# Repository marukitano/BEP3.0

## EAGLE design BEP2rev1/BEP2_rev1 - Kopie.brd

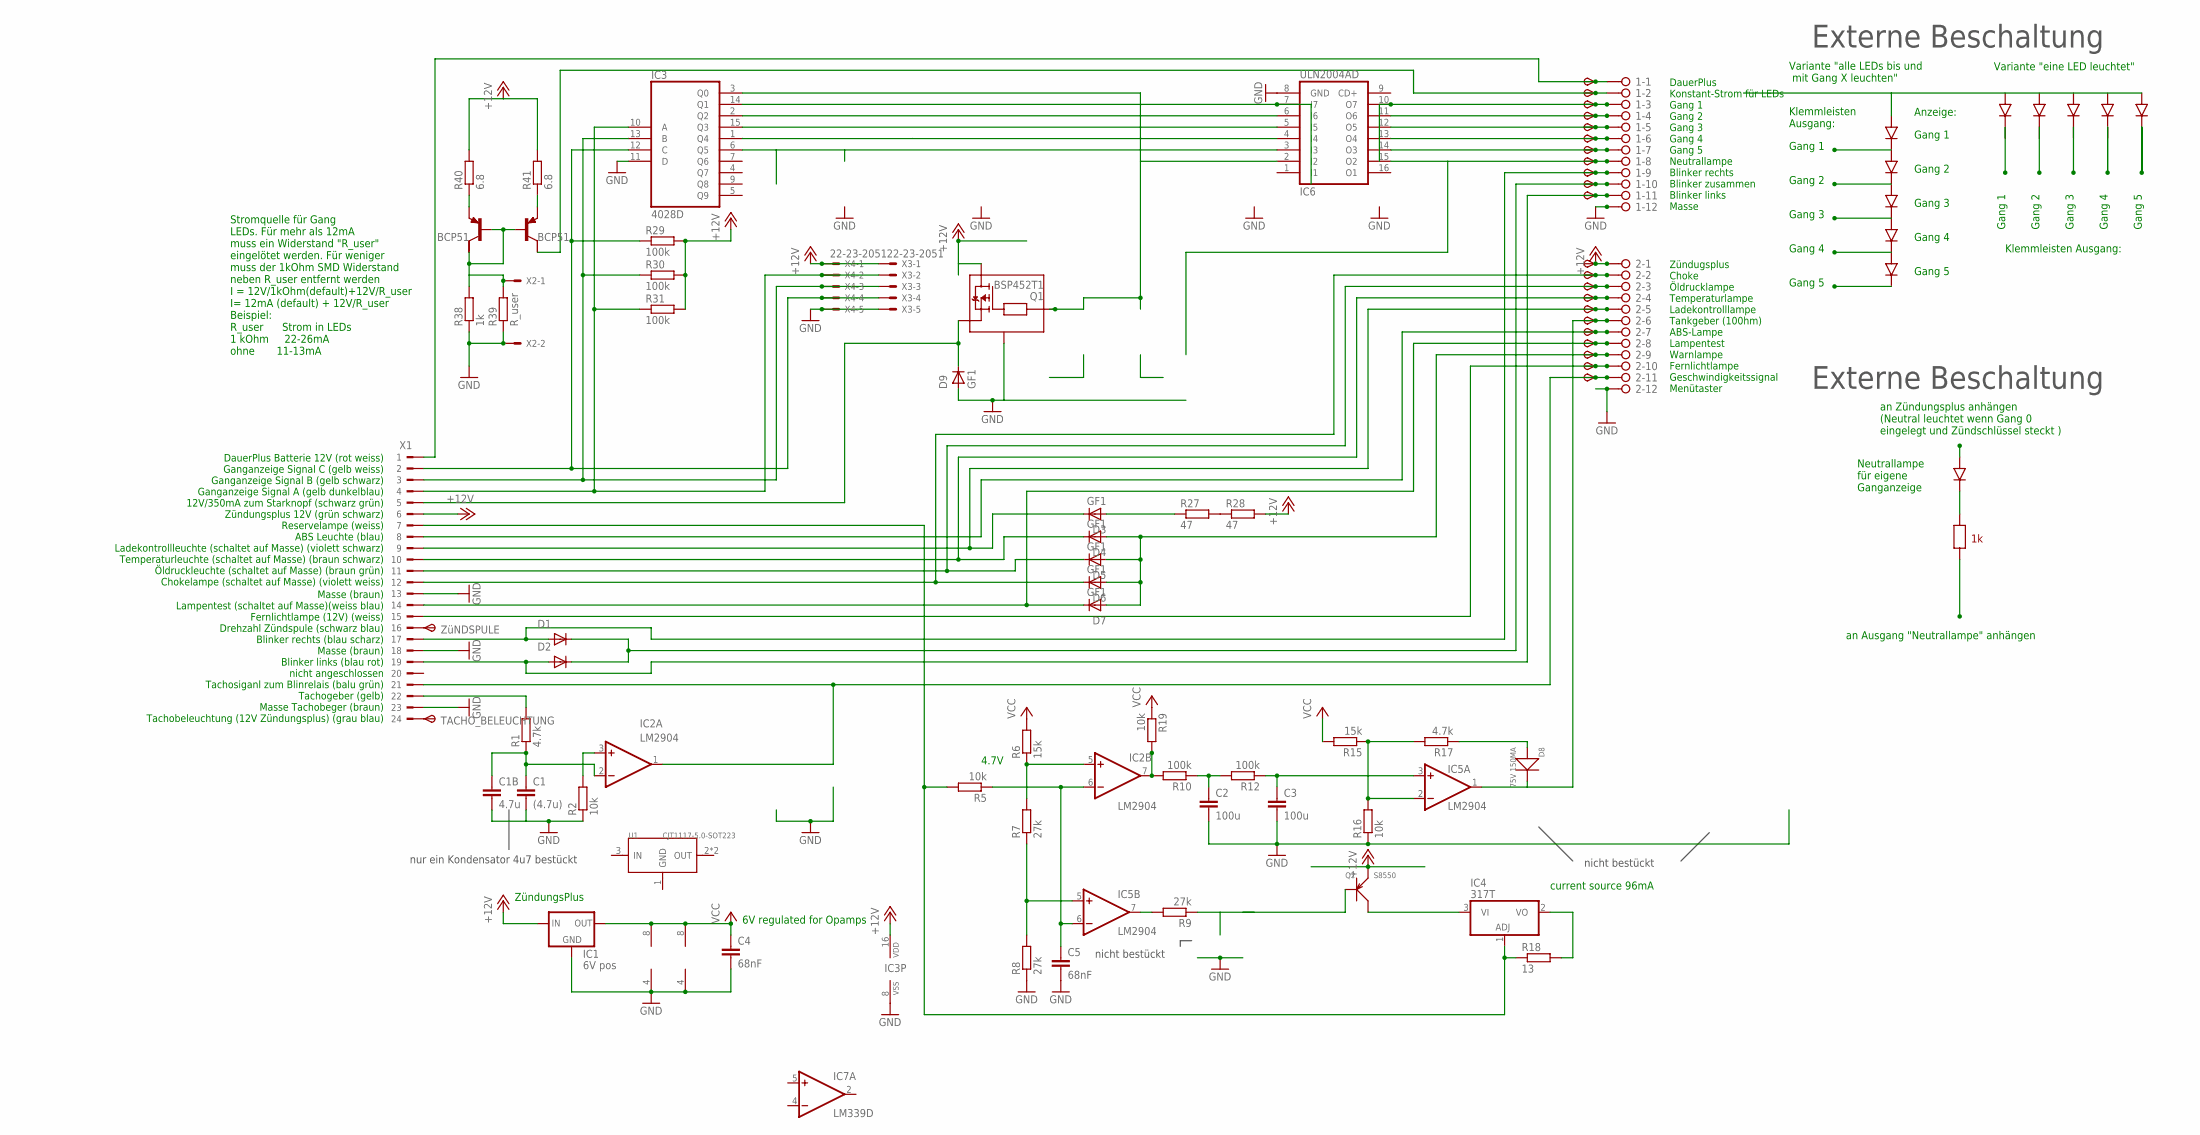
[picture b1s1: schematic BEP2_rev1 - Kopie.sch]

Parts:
1, 2: 2081-1132; 12-PIN
C1: (4.7u); C1206
C1B: 4.7u; C0805K
C2, C3: 100u; C1206K
C4, C5: 68nF; C1206K
D1, D2, D3, D4, D5, D6, D7, D9: GF1; SMA-DO214AC
D8: 75V 150MA; LED-1206
IC1: 6V pos; 78LXX
IC2, IC5: LM2904; SO08
IC3: 4028D; SO16
IC4: 317T; TO220H
IC6: ULN2004AD; SO16
IC7: LM339D; SO14
Q1: BSP452T1; SOT223
Q2: S8550; SOT-23
R1, R17: 4.7k; R0805
R2, R5, R16, R19: 10k; R0805
R6, R15: 15k; R0805
R7, R8, R9: 27k; R0805
R10, R12, R29, R30, R31: 100k; R0805
R18: 13; 0207/10
R27, R28: 47; V235/17
R38: 1k; R0805
R39: R_user; R0805
R40, R41: 6.8; R0805
T13, T14: BCP53T1; SOT223
TACHO_BELEUCHTUNG: TPSP1_1MM; P1_1.0MM
TP1, TP2, TP3, TP4, TP5, TP6, TP7, TP8, TP9, TP10, TP11, TP12, TP16, TP17, TP18, TP19, TP21, TP22, TP23, TP24, TP25, TP26: TPSB1,27; B1,27
U1: CJT1117-5.0-SOT223; SOT-223
X1: CON_BMW; 24-PIN
X2: 22-23-2021
X3, X4: 22-23-2051
ZüNDSPULE: TPSP1_1MM; P1_1.0MM

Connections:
+12V: 2.1, IC1.IN, IC3.16 (VDD), Q1.4 (V+), Q2.2 (E), R28.2, R29.2, R30.2, R31.2, R40.2, R41.2, TP12.TP, X1.6, X3.1, X4.1
GND: 1.12, 2.12, C1.2, C1B.2, C2.2, C3.2, C4.2, C5.2, D9.A, IC1.GND, IC2.4 (V-), IC3.8 (VSS), IC3.11 (D), IC5.4 (V-), IC6.8 (GND), IC7.12 (GND), Q1.2 (GND), R2.1, R8.1, R16.1, R38.1, R39.1, X1.13, X1.18, X1.23, X2.2, X3.5, X4.5
unnamed: 2.9, D4.A, D5.A, D6.A, D7.A, TP24.TP
unnamed: IC3.10 (A), R31.1, X1.4, X3.2, X4.2
unnamed: IC3.13 (B), R30.1, X1.3, X3.3, X4.3
unnamed: 2.7, TP22.TP, X1.8
unnamed: IC3.3 (Q0), IC6.2 (I2), Q1.3 (IN)
unnamed: IC2.3 (+IN), R2.2
unnamed: R27.2, R28.1
unnamed: D9.K (C), Q1.1 (OUT), X1.5
unnamed: 2.2, D6.K (C), TP16.TP, X1.12
unnamed: 2.3, D5.K (C), TP17.TP, X1.11
unnamed: 2.4, D4.K (C), TP18.TP, X1.10
unnamed: IC4.1 (ADJ), R5.2, R18.1, X1.7
unnamed: C5.1, IC2.6 (-IN), IC5.6 (-IN), R5.1
unnamed: IC3.12 (C), R29.1, X1.2, X3.4, X4.4
unnamed: IC3.15 (Q3), IC6.5 (I5)
unnamed: 2.8, D7.K (C), TP23.TP, X1.14
unnamed: 1.9, D1.A, TP9.TP, X1.17
unnamed: 1.11, D2.A, TP11.TP, X1.19
unnamed: 1.10, D1.K (C), D2.K (C), TP10.TP
unnamed: R1.2, X1.22
unnamed: C1.1, C1B.1, IC2.2 (-IN), R1.1
unnamed: 1.6, IC6.13 (O4), TP6.TP
unnamed: 1.7, IC6.14 (O3), TP7.TP
unnamed: 2.11, IC2.1 (OUT), TP26.TP, X1.21
unnamed: IC4.2 (VO), R18.2
unnamed: IC5.5 (+IN), R7.1, R8.2
unnamed: IC5.7 (OUT), R9.2
unnamed: IC4.3 (VI), Q2.3 (C)
unnamed: Q2.1 (B), R9.1
unnamed: IC3.14 (Q1), IC6.7 (I7)
unnamed: IC3.2 (Q2), IC6.6 (I6)
unnamed: 1.5, IC6.12 (O5), TP5.TP
unnamed: IC2.5 (+IN), R6.1, R7.2
unnamed: IC2.7 (OUT), R10.2, R19.2
unnamed: X1.16, ZüNDSPULE.TP
unnamed: C2.1, R10.1, R12.2
unnamed: C3.1, IC5.3 (+IN), R12.1
unnamed: IC5.2 (-IN), R15.1, R16.2, R17.2
unnamed: D8.+, R17.1
unnamed: 1.8, IC6.15 (O2), TP8.TP
unnamed: 2.10, TP25.TP, X1.15
unnamed: D3.A, R27.1
unnamed: 2.5, D3.K (C), TP19.TP, X1.9
unnamed: TACHO_BELEUCHTUNG.TP, X1.24
unnamed: 1.2, T14.2 (C), TP2.TP
unnamed: 2.6, D8.-, IC5.1 (OUT), TP21.TP
unnamed: IC3.6 (Q5), IC6.3 (I3)
unnamed: 1.4, IC6.11 (O6), TP4.TP
unnamed: 1.3, IC6.10 (O7), TP3.TP
unnamed: R38.2, R39.2, T13.1 (B), T13.2 (C), T14.1 (B), X2.1
unnamed: 1.1, TP1.TP, X1.1
unnamed: R40.1, T13.3 (E)
unnamed: R41.1, T14.3 (E)
V+: IC7.3 (V+)
VCC: C4.1, IC1.OUT, IC2.8 (V+), IC5.8 (V+), R6.2, R15.2, R19.1

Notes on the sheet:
6V regulated for Opamps
current source 96mA
ZündungsPlus
Zündugsplus Choke Öldrucklampe Temperaturlampe Ladekontrolllampe Tankgeber (100hm) ABS-Lampe Lampentest Warnlampe Fernlichtlampe Geschwindigkeitssignal Menütaster
DauerPlus Konstant-Strom für LEDs Gang 1 Gang 2 Gang 3 Gang 4 Gang 5 Neutrallampe Blinker rechts Blinker zusammen Blinker links Masse
DauerPlus Batterie 12V (rot weiss) Ganganzeige Signal C (gelb weiss) Ganganzeige Signal B (gelb schwarz) Ganganzeige Signal A (gelb dunkelblau) 12V/350mA zum Starknopf (schwarz grün) Zündungsplus 12V (grün schwarz) Reservelampe (weiss) ABS Leuchte (blau) Ladekontrollleuchte (schaltet auf Masse) (vi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
Masse (braun) Lampentest (schaltet auf Masse)(weiss blau) Fernlichtlampe (12V) (weiss) Drehzahl Zündspule (schwarz blau) Blinker rechts (blau scharz) Masse (braun) Blinker links (blau rot) nicht angeschlossen Tachosiganl zum Blinrelais (balu grün) Tachogeber (gelb) Masse Tachobeger (braun) Tachobel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
4.7V
Stromquelle für Gang LEDs. Für mehr als 12mA muss ein Widerstand "R_user" eingelötet werden. Für weniger muss der 1kOhm SMD Widerstand neben R_user entfernt werden I = 12V/1kOhm(default)+12V/R_user I= 12mA (default) + 12V/R_user Beispiel: R_user Strom in LEDs 1 kOhm 22-26mA ohne 11-13mA
Gang 1
Gang 2
Gang 3
Gang 4
Gang 5
Variante "eine LED leuchtet"
Variante "alle LEDs bis und mit Gang X leuchten"
Klemmleisten Ausgang:
Klemmleisten Ausgang:
an Zündungsplus anhängen (Neutral leuchtet wenn Gang 0 eingelegt und Zündschlüssel steckt )
an Ausgang "Neutrallampe" anhängen
Neutrallampe für eigene Ganganzeige
Externe Beschaltung
Anzeige:
nicht bestückt
nur ein Kondensator 4u7 bestückt

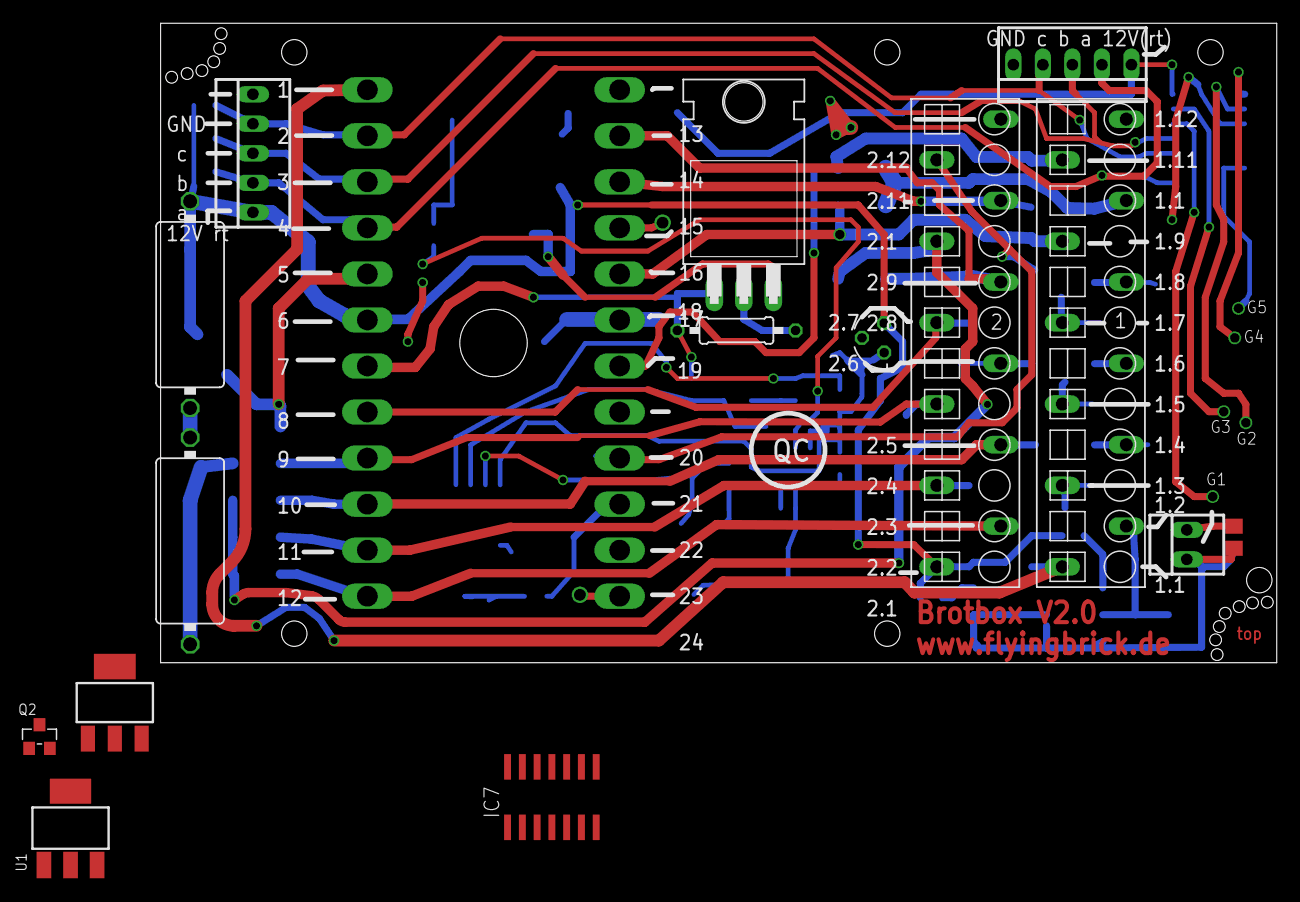
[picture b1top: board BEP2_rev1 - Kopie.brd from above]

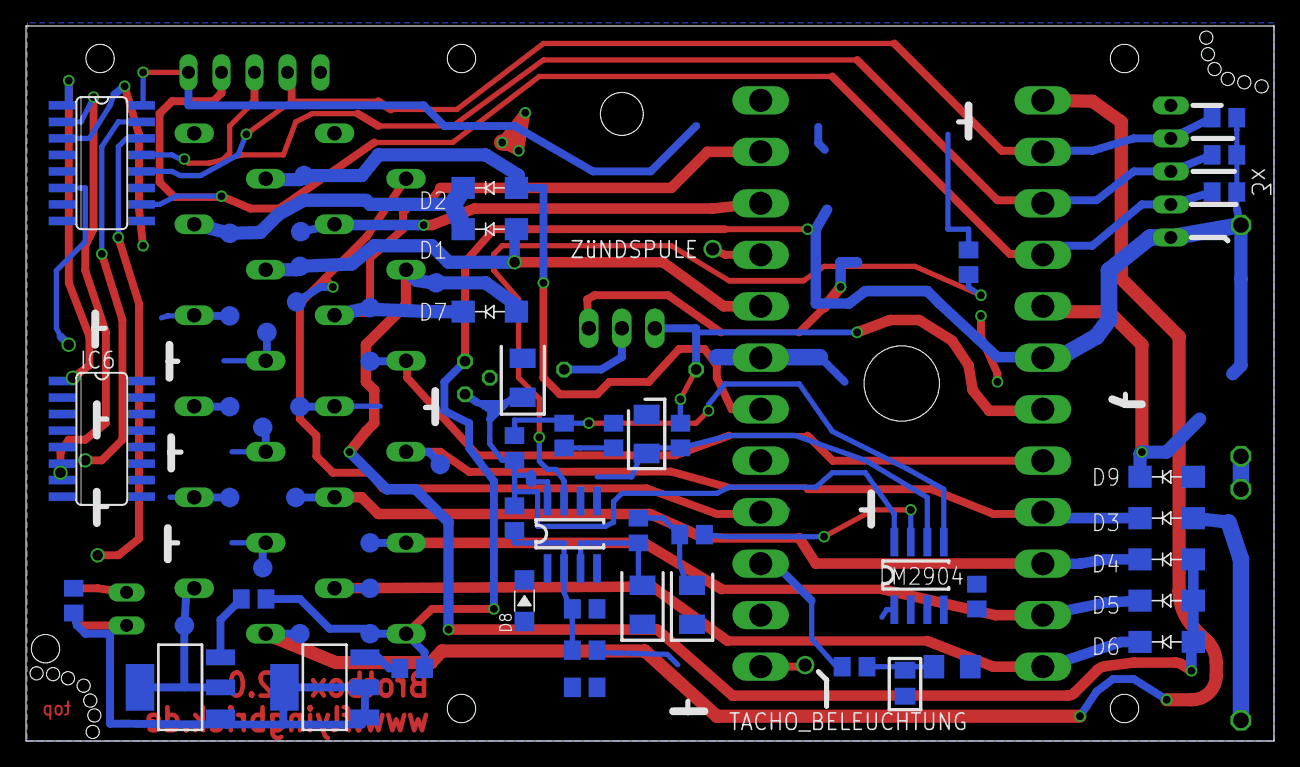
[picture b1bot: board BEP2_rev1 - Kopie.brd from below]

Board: 2 copper layers, 96.0 x 55.0 mm, 80 parts (64 on the bottom side), 56 nets.

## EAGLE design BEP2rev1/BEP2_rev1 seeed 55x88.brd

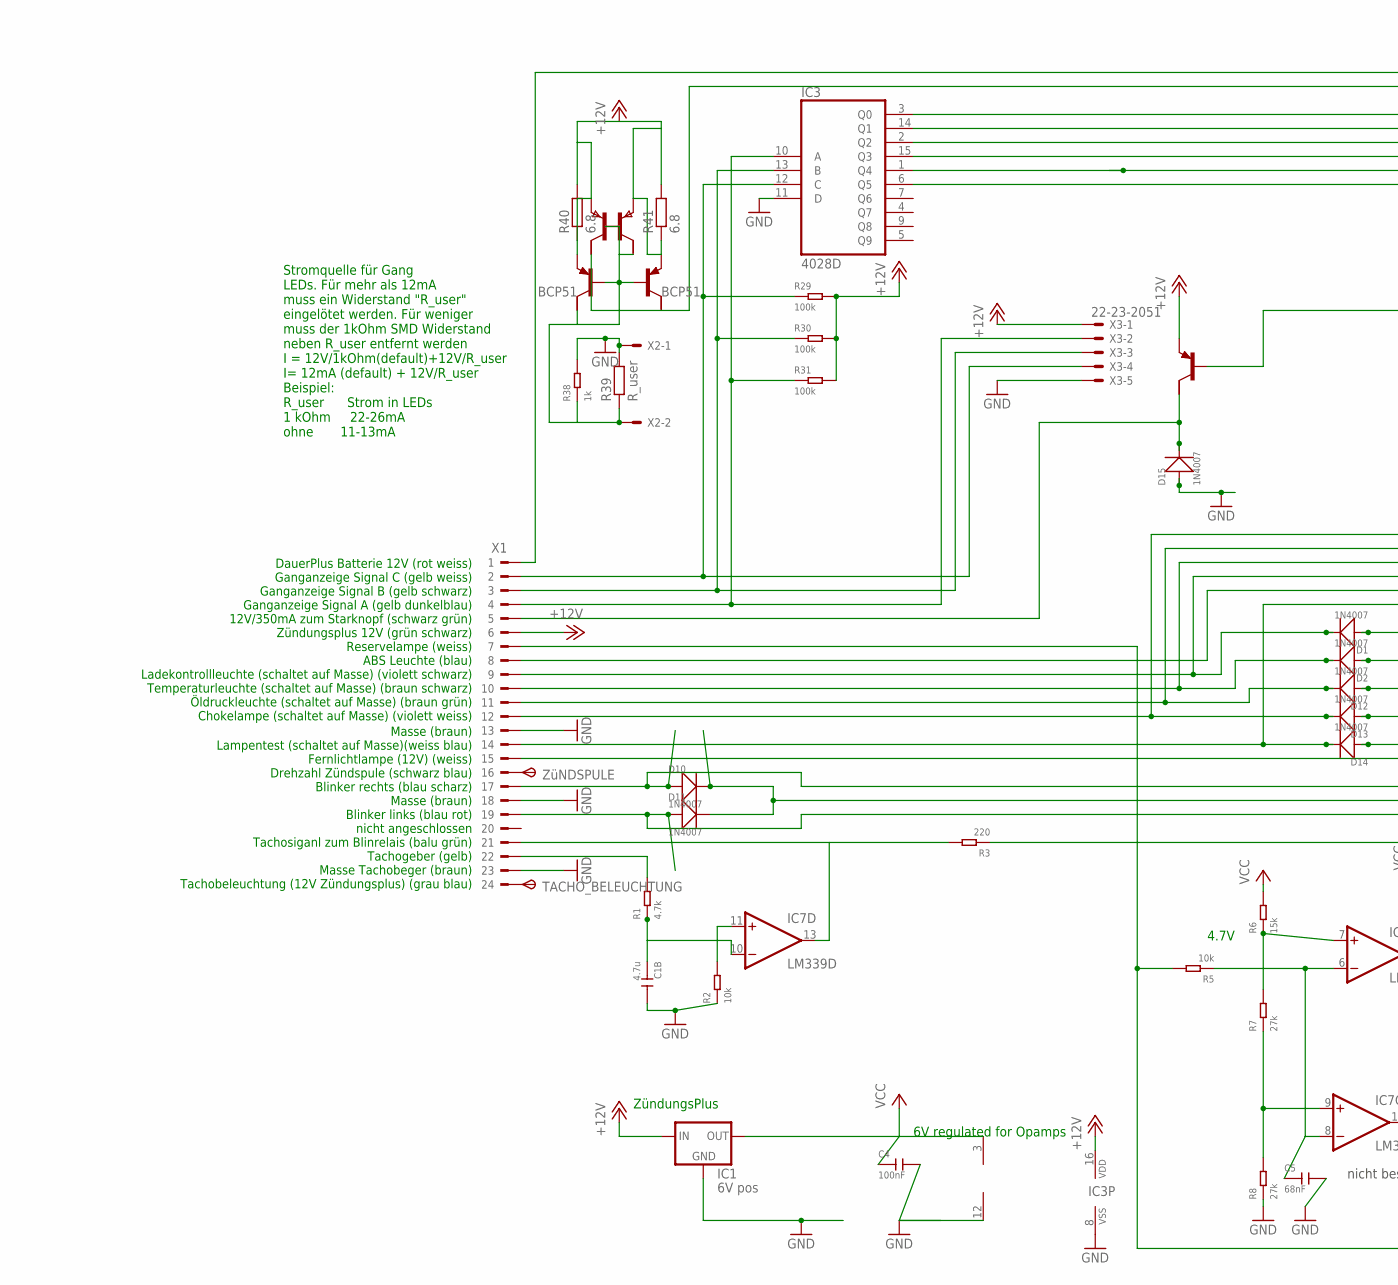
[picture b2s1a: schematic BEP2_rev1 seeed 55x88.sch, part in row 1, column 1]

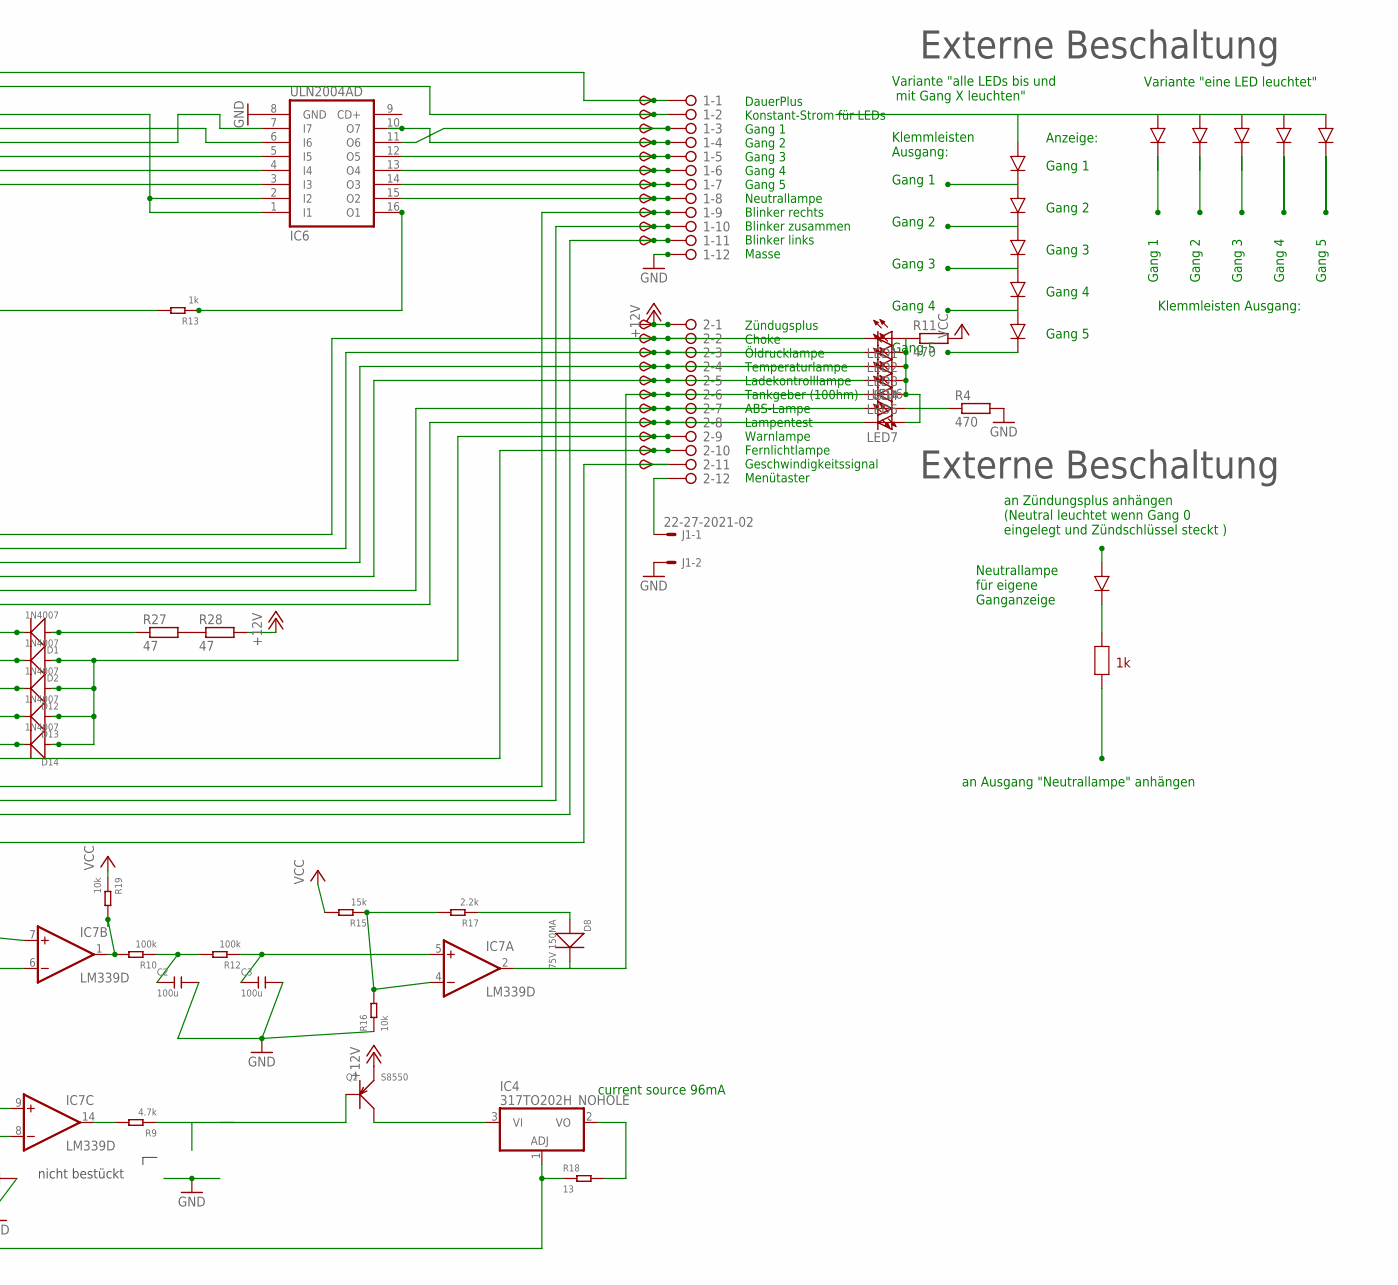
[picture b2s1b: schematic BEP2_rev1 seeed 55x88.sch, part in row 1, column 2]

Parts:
1, 2: 2081-1132; 12-PIN
C1B: 4.7u; C0805
C2, C3: 100u; C1206
C4: 100nF; C0805
C5: 68nF; C0805
D1, D2, D10, D11, D12, D13, D14, D15: 1N4007; DO-214AC
D8: 75V 150MA; LED-1206
IC1: 6V pos; 78LXX
IC3: 4028D; SO16
IC4: 317TO202H_NOHOLE; TO220H_NOHOLE
IC6: ULN2004AD; SO16
IC7: LM339D; SO14
J1: 22-27-2021-02; 6410-02
LED1, LED2, LED3, LED4, LED5, LED6, LED7: LEDLD260; LD260
Q2: S8550; SOT-23
Q3: BCP53T1; SOT223
R1, R9: 4.7k; R0805
R2, R5, R16, R19: 10k; R0805
R3: 220; R0805
R4, R11: 470; R0805
R6: 15k; R0805
R7, R8: 27k; R0603
R10, R12, R29, R30, R31: 100k; R0603
R13, R38: 1k; R0805
R15: 15k; R0603
R17: 2.2k; R0805
R18: 13; R1206
R27, R28: 47; V235/17_1MM
R39: R_user; R0805
R40, R41: 6.8; R0805
T1: PNP2SM8; SM8
T13, T14: BCP53T1; SOT223
TACHO_BELEUCHTUNG: TPSP1_1MM; P1_1.0MM
TP1, TP2, TP3, TP4, TP5, TP6, TP7, TP8, TP9, TP10, TP11, TP12, TP16, TP17, TP18, TP19, TP21, TP22, TP23, TP24, TP25, TP26: TPSB1,27; B1,27
X1: CON_BMW; 24-PIN
X2: 22-23-2021
X3: 22-23-2051
ZüNDSPULE: TPSP1_1MM; P1_1.0MM

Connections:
+12V: 2.1, IC1.IN, IC3.16 (VDD), Q2.2 (E), Q3.3 (E), R28.2, R29.2, R30.2, R31.2, R40.1, R40.2, R41.1, R41.2, T1.1 (E), T1.3 (E), T13.3 (E), T14.3 (E), TP12.TP, X1.6, X3.1
GND: 1.12, C1B.2, C2.2, C3.2, C4.2, C5.2, D15.1 (+), IC1.GND, IC3.8 (VSS), IC3.11 (D), IC6.8 (GND), IC7.12 (GND), J1.2, R2.1, R4.2, R8.1, R16.1, R38.2, R39.2, X1.13, X1.18, X1.23, X2.1, X3.5
unnamed: 2.9, D2.1 (+), D12.1 (+), D13.1 (+), D14.1 (+), TP24.TP
unnamed: IC3.10 (A), R31.1, X1.4, X3.2
unnamed: IC3.13 (B), R30.1, X1.3, X3.3
unnamed: 2.7, LED6.A, TP22.TP, X1.8
unnamed: IC6.16 (O1), R13.1
unnamed: IC7.11 (+IN), R2.2
unnamed: R27.2, R28.1
unnamed: D15.2 (-), Q3.2 (C), X1.5
unnamed: 2.2, D13.2 (-), LED1.K (C), TP16.TP, X1.12
unnamed: 2.3, D12.2 (-), LED2.K (C), TP17.TP, X1.11
unnamed: 2.4, D2.2 (-), LED3.K (C), TP18.TP, X1.10
unnamed: IC4.1 (ADJ), R5.2, R18.1, X1.7
unnamed: C5.1, IC7.6 (-IN), IC7.8 (-IN), R5.1
unnamed: IC3.12 (C), R29.1, X1.2, X3.4
unnamed: IC3.15 (Q3), IC6.5 (I5)
unnamed: 2.8, D14.2 (-), LED7.K (C), TP23.TP, X1.14
unnamed: 1.9, D10.1 (+), TP9.TP, X1.17
unnamed: 1.11, D11.1 (+), TP11.TP, X1.19
unnamed: 1.10, D10.2 (-), D11.2 (-), TP10.TP
unnamed: R1.2, X1.22
unnamed: C1B.1, IC7.10 (-IN), R1.1
unnamed: 1.6, IC6.13 (O4), TP6.TP
unnamed: 1.7, IC6.14 (O3), TP7.TP
unnamed: 2.11, R3.1, TP26.TP
unnamed: 2.12, J1.1
unnamed: IC4.2 (VO), R18.2
unnamed: IC7.9 (+IN), R7.1, R8.2
unnamed: IC7.14 (OUT), R9.2
unnamed: LED6.K (C), R4.1
unnamed: IC4.3 (VI), Q2.3 (C)
unnamed: Q2.1 (B), R9.1
unnamed: IC3.2 (Q2), IC6.7 (I7)
unnamed: 1.3, IC6.11 (O6), TP3.TP
unnamed: 1.5, IC6.12 (O5), TP5.TP
unnamed: IC7.7 (+IN), R6.1, R7.2
unnamed: LED1.A, LED2.A, LED3.A, LED4.A, LED5.A, LED7.A, R11.1
unnamed: X1.16, ZüNDSPULE.TP
unnamed: Q3.1 (B), R13.2
unnamed: IC3.3 (Q0), IC6.1 (I1), IC6.2 (I2)
unnamed: C2.1, R10.1, R12.2
unnamed: C3.1, IC7.5 (+IN), R12.1
unnamed: IC7.4 (-IN), R15.1, R16.2, R17.2
unnamed: IC7.13 (OUT), R3.2, X1.21
unnamed: D8.+, R17.1
unnamed: IC3.1 (Q4), IC6.4 (I4)
unnamed: 1.8, IC6.15 (O2), TP8.TP
unnamed: 2.10, TP25.TP, X1.15
unnamed: D1.1 (+), R27.1
unnamed: 2.5, D1.2 (-), LED4.K (C), TP19.TP, X1.9
unnamed: IC3.14 (Q1), IC6.6 (I6)
unnamed: R38.1, R39.1, T1.2 (B), T1.4 (B), T1.6 (C1), T13.1 (B), T13.2 (C), T14.1 (B), X2.2
unnamed: TACHO_BELEUCHTUNG.TP, X1.24
unnamed: 1.2, T1.8 (C1), T14.2 (C), TP2.TP
unnamed: 2.6, D8.-, IC7.2 (OUT), LED5.K (C), TP21.TP
unnamed: IC3.6 (Q5), IC6.3 (I3)
unnamed: 1.4, IC6.10 (O7), TP4.TP
unnamed: 1.1, TP1.TP, X1.1
unnamed: IC7.1 (OUT), R10.2, R19.2
VCC: C4.1, IC1.OUT, IC7.3 (V+), R6.2, R11.2, R15.2, R19.1

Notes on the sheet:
6V regulated for Opamps
current source 96mA
ZündungsPlus
Zündugsplus Choke Öldrucklampe Temperaturlampe Ladekontrolllampe Tankgeber (100hm) ABS-Lampe Lampentest Warnlampe Fernlichtlampe Geschwindigkeitssignal Menütaster
DauerPlus Konstant-Strom für LEDs Gang 1 Gang 2 Gang 3 Gang 4 Gang 5 Neutrallampe Blinker rechts Blinker zusammen Blinker links Masse
DauerPlus Batterie 12V (rot weiss) Ganganzeige Signal C (gelb weiss) Ganganzeige Signal B (gelb schwarz) Ganganzeige Signal A (gelb dunkelblau) 12V/350mA zum Starknopf (schwarz grün) Zündungsplus 12V (grün schwarz) Reservelampe (weiss) ABS Leuchte (blau) Ladekontrollleuchte (schaltet auf Masse) (vi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
Masse (braun) Lampentest (schaltet auf Masse)(weiss blau) Fernlichtlampe (12V) (weiss) Drehzahl Zündspule (schwarz blau) Blinker rechts (blau scharz) Masse (braun) Blinker links (blau rot) nicht angeschlossen Tachosiganl zum Blinrelais (balu grün) Tachogeber (gelb) Masse Tachobeger (braun) Tachobel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
4.7V
Stromquelle für Gang LEDs. Für mehr als 12mA muss ein Widerstand "R_user" eingelötet werden. Für weniger muss der 1kOhm SMD Widerstand neben R_user entfernt werden I = 12V/1kOhm(default)+12V/R_user I= 12mA (default) + 12V/R_user Beispiel: R_user Strom in LEDs 1 kOhm 22-26mA ohne 11-13mA
Gang 1
Gang 2
Gang 3
Gang 4
Gang 5
Variante "eine LED leuchtet"
Variante "alle LEDs bis und mit Gang X leuchten"
Klemmleisten Ausgang:
Klemmleisten Ausgang:
an Zündungsplus anhängen (Neutral leuchtet wenn Gang 0 eingelegt und Zündschlüssel steckt )
an Ausgang "Neutrallampe" anhängen
Neutrallampe für eigene Ganganzeige
Externe Beschaltung
Anzeige:
nicht bestückt

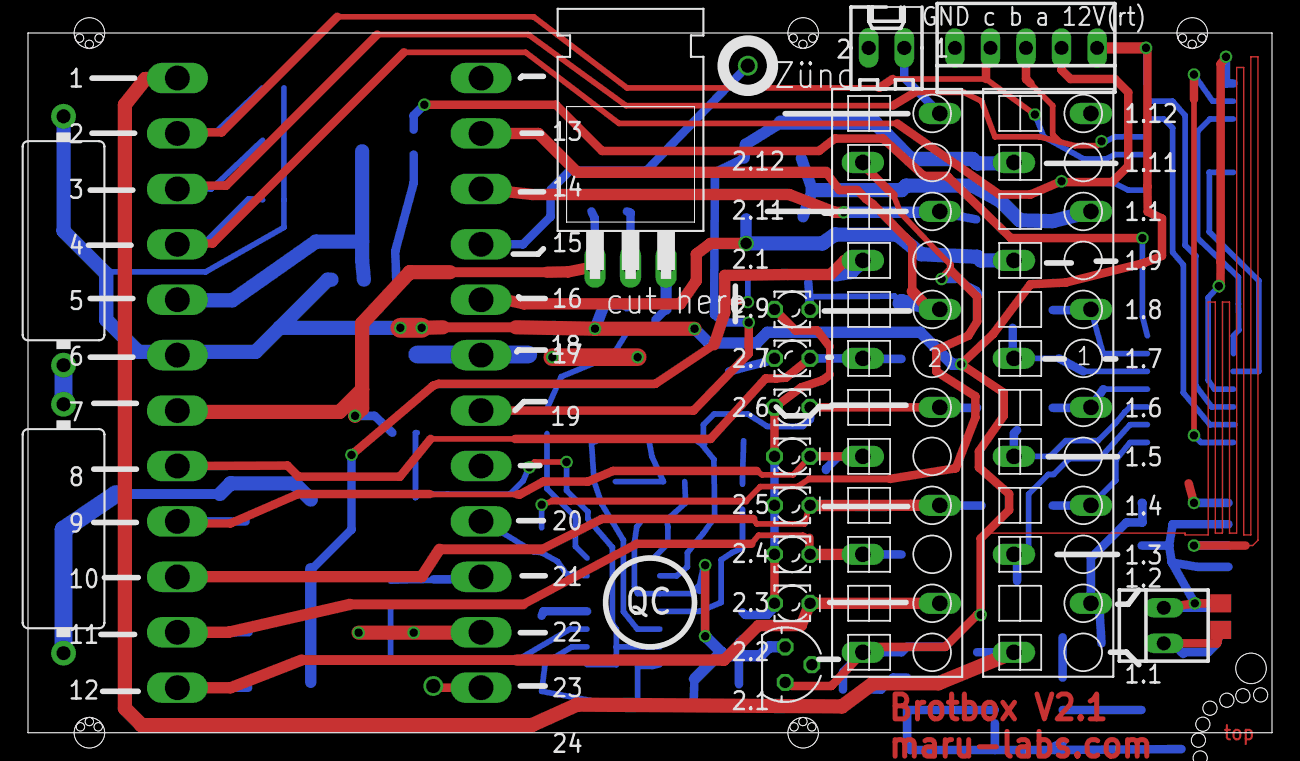
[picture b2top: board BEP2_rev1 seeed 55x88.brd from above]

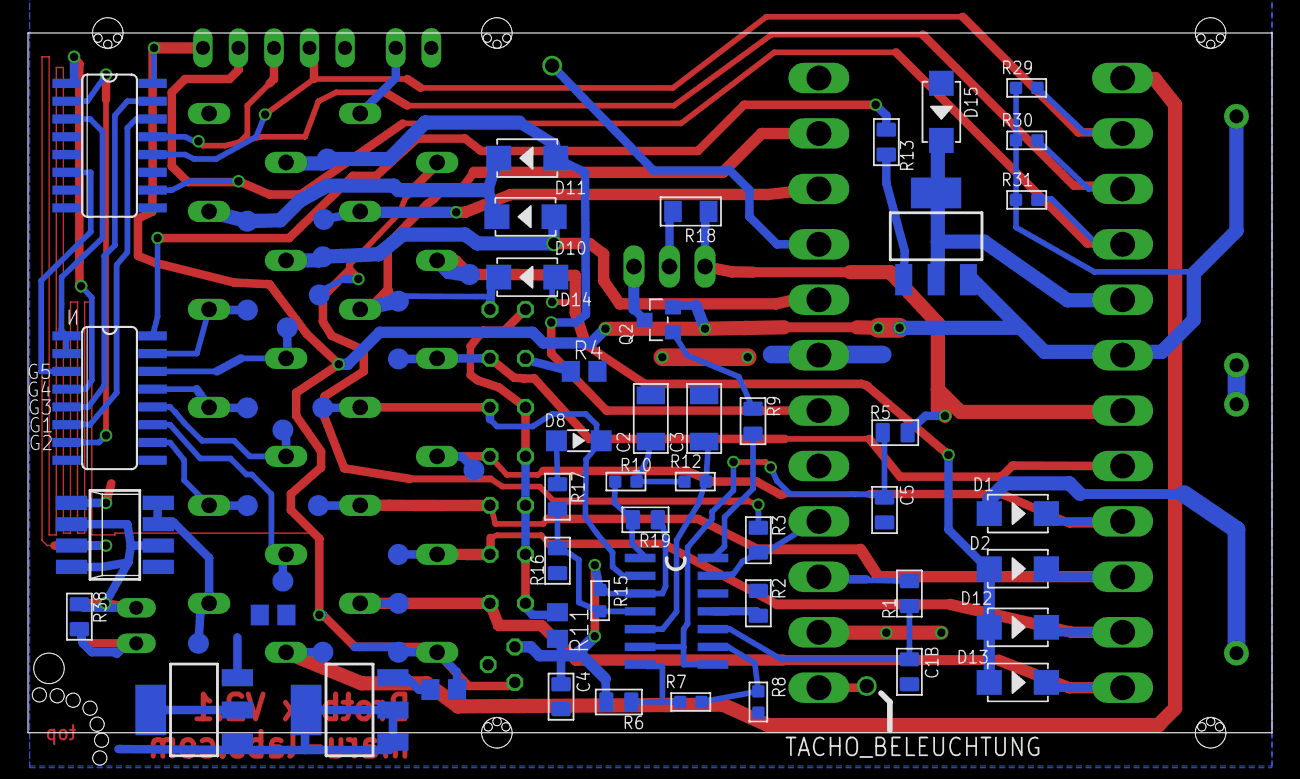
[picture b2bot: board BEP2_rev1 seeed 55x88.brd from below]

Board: 2 copper layers, 88.9 x 50.0 mm, 88 parts (70 on the bottom side), 61 nets.

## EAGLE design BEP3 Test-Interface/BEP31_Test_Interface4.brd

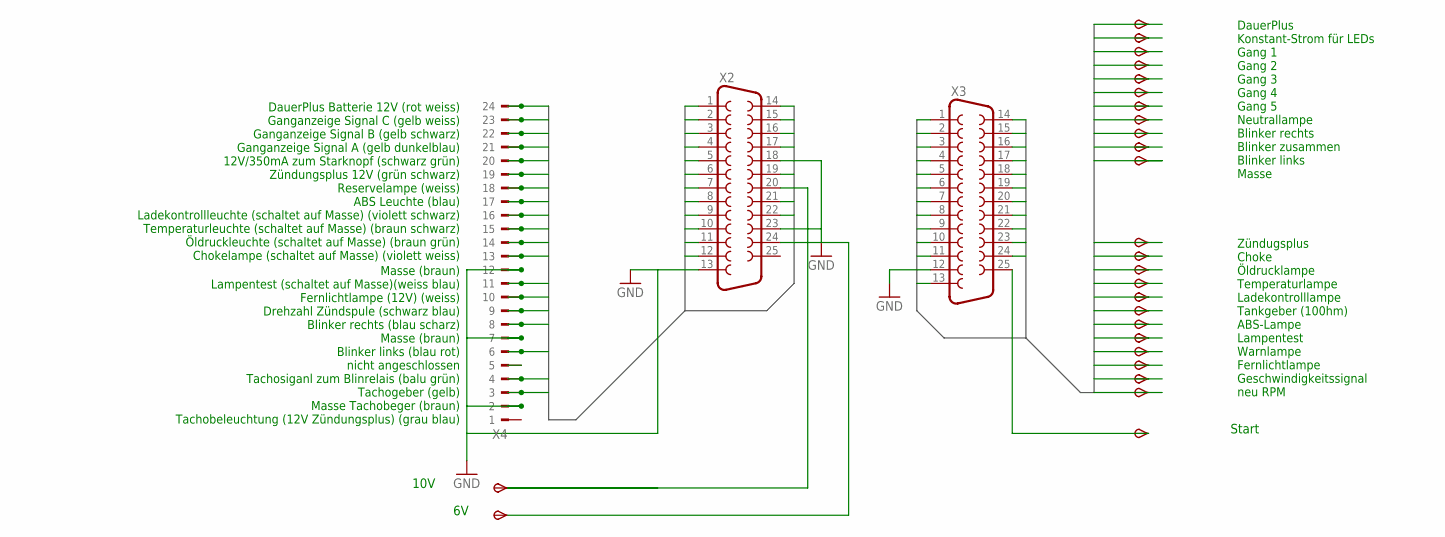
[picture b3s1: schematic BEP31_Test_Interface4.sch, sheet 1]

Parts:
TP1, TP2, TP3, TP4, TP5, TP6, TP7, TP8, TP9, TP10, TP11, TP12, TP13, TP14, TP15_10V, TP16, TP17, TP18, TP19, TP20_6V, TP21, TP22, TP23, TP24, TP25, TP26: TPSFEDERPIN; 1,36ID
X2, X3: F25H
X4: CON_BMWTESTPINS; 24-TESTPIN_1,36ID

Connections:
BMW1: X2.1, X4.P24 (24)
BMW2: X2.2, X4.P23 (23)
BMW3: X2.3, X4.P22 (22)
BMW4: X2.4, X4.P21 (21)
BMW5: X2.5, X4.P20 (20)
BMW6: X2.6, X4.P19 (19)
BMW7: X2.7, X4.P18 (18)
BMW8: X2.8, X4.P17 (17)
BMW9: X2.9, X4.P16 (16)
BMW10: X2.10, X4.P15 (15)
BMW11: X2.11, X4.P14 (14)
BMW12: X2.12, X4.P13 (13)
BMW14: X2.14, X4.P11 (11)
BMW15: X2.15, X4.P10 (10)
BMW16: X2.16, X4.P9 (9)
BMW17: X2.17, X4.P8 (8)
BMW19: X2.19, X4.P6 (6)
BMW21: X2.21, X4.P4 (4)
BMW22: X2.22, X4.P3 (3)
BMW24: TP15_10V.P$1, X2.20
GND: X2.13, X2.18, X2.23, X3.12, X4.P2 (2), X4.P7 (7), X4.P12 (12)
unnamed: TP14.P$1, X3.25
unnamed: TP20_6V.P$1, X2.24
WAGO1: TP1.P$1, X3.1
WAGO2: TP2.P$1, X3.2
WAGO3: TP3.P$1, X3.3
WAGO4: TP4.P$1, X3.4
WAGO5: TP5.P$1, X3.5
WAGO6: TP6.P$1, X3.6
WAGO7: TP7.P$1, X3.7
WAGO8: TP8.P$1, X3.8
WAGO9: TP9.P$1, X3.9
WAGO10: TP10.P$1, X3.10
WAGO11: TP11.P$1, X3.11
WAGO13: TP12.P$1, X3.13
WAGO14: TP16.P$1, X3.14
WAGO15: TP17.P$1, X3.15
WAGO16: TP18.P$1, X3.16
WAGO17: TP19.P$1, X3.17
WAGO18: TP21.P$1, X3.18
WAGO19: TP22.P$1, X3.19
WAGO20: TP23.P$1, X3.20
WAGO21: TP24.P$1, X3.21
WAGO22: TP25.P$1, X3.22
WAGO23: TP26.P$1, X3.23
WAGO24: TP13.P$1, X3.24

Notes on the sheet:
Zündugsplus Choke Öldrucklampe Temperaturlampe Ladekontrolllampe Tankgeber (100hm) ABS-Lampe Lampentest Warnlampe Fernlichtlampe Geschwindigkeitssignal neu RPM
DauerPlus Konstant-Strom für LEDs Gang 1 Gang 2 Gang 3 Gang 4 Gang 5 Neutrallampe Blinker rechts Blinker zusammen Blinker links Masse
DauerPlus Batterie 12V (rot weiss) Ganganzeige Signal C (gelb weiss) Ganganzeige Signal B (gelb schwarz) Ganganzeige Signal A (gelb dunkelblau) 12V/350mA zum Starknopf (schwarz grün) Zündungsplus 12V (grün schwarz) Reservelampe (weiss) ABS Leuchte (blau) Ladekontrollleuchte (schaltet auf Masse) (vi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
Masse (braun) Lampentest (schaltet auf Masse)(weiss blau) Fernlichtlampe (12V) (weiss) Drehzahl Zündspule (schwarz blau) Blinker rechts (blau scharz) Masse (braun) Blinker links (blau rot) nicht angeschlossen Tachosiganl zum Blinrelais (balu grün) Tachogeber (gelb) Masse Tachobeger (braun) Tachobel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
Start
10V

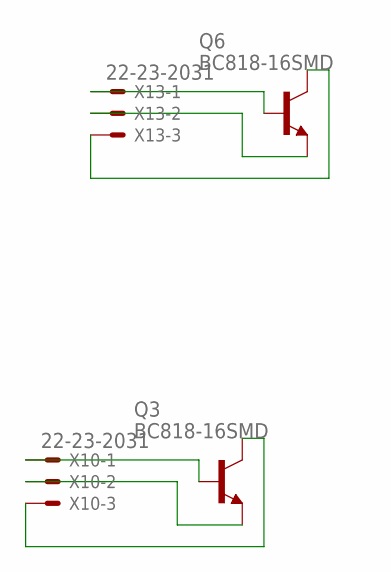
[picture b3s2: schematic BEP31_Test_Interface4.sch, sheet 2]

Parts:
Q3, Q6: BC818-16SMD; SOT23-BEC
X10, X13: 22-23-2031

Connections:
unnamed: Q3.B, X10.1
unnamed: Q3.E, X10.2
unnamed: Q3.C, X10.3
unnamed: Q6.B, X13.1
unnamed: Q6.E, X13.2
unnamed: Q6.C, X13.3

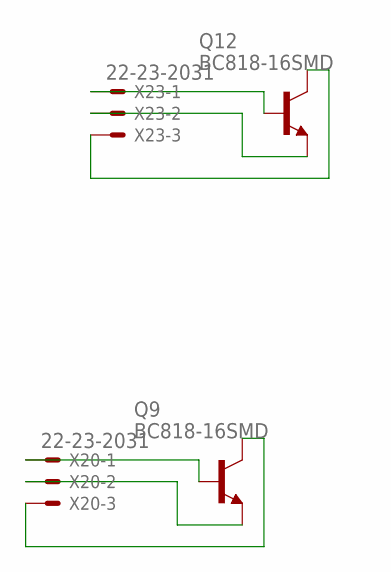
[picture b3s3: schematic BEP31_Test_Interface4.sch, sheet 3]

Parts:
Q9, Q12: BC818-16SMD; SOT23-BEC
X20, X23: 22-23-2031

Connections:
unnamed: Q9.B, X20.1
unnamed: Q9.E, X20.2
unnamed: Q9.C, X20.3
unnamed: Q12.B, X23.1
unnamed: Q12.E, X23.2
unnamed: Q12.C, X23.3

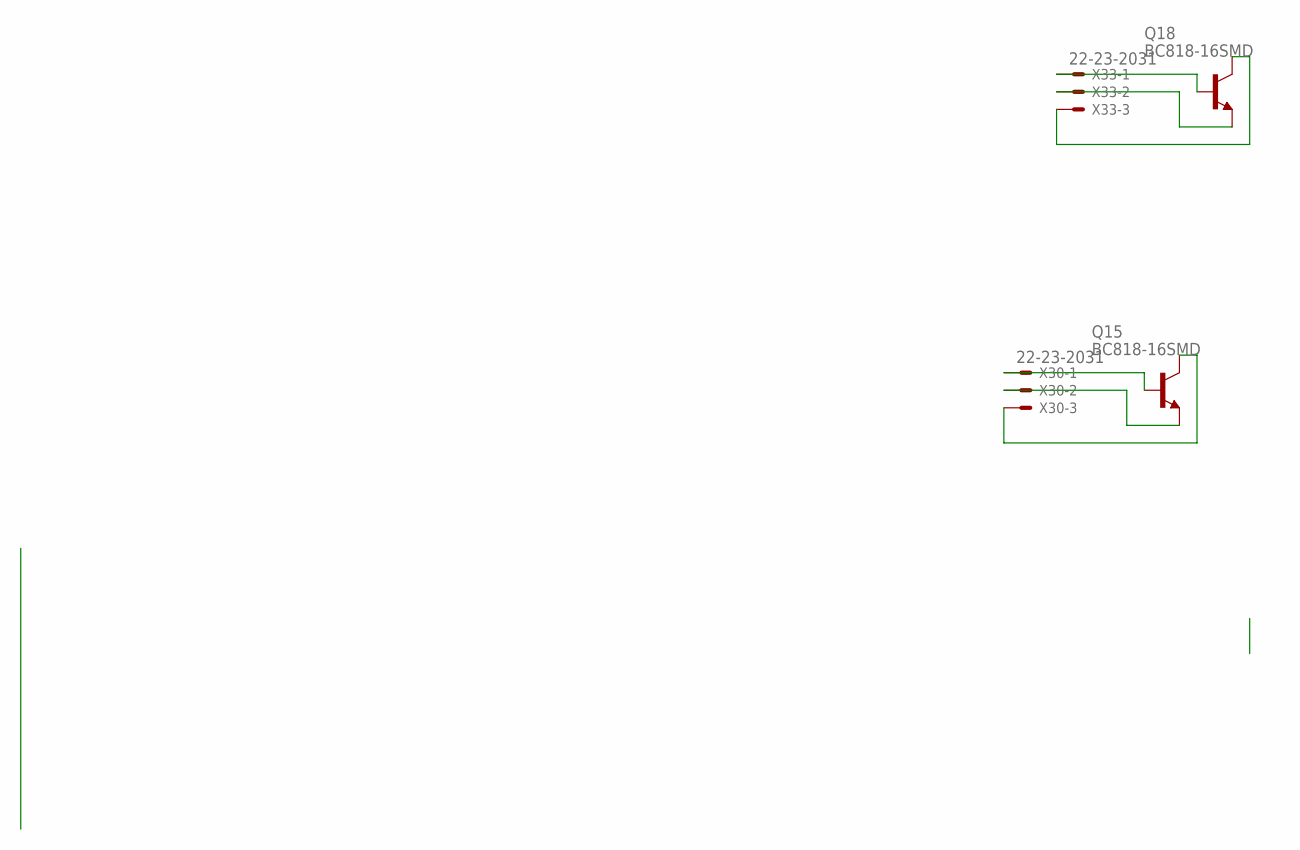
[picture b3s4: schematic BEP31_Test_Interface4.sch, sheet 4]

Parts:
Q15, Q18: BC818-16SMD; SOT23-BEC
X30, X33: 22-23-2031

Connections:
unnamed: Q15.B, X30.1
unnamed: Q15.E, X30.2
unnamed: Q15.C, X30.3
unnamed: Q18.B, X33.1
unnamed: Q18.E, X33.2
unnamed: Q18.C, X33.3

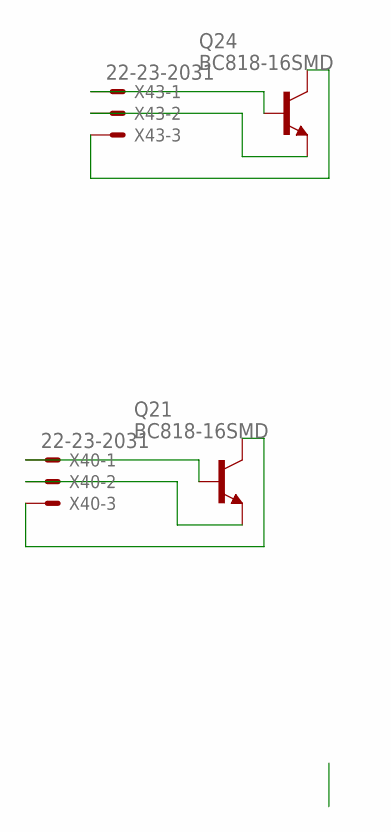
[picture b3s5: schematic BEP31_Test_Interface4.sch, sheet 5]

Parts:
Q21, Q24: BC818-16SMD; SOT23-BEC
X40, X43: 22-23-2031

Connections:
unnamed: Q21.B, X40.1
unnamed: Q21.E, X40.2
unnamed: Q21.C, X40.3
unnamed: Q24.B, X43.1
unnamed: Q24.E, X43.2
unnamed: Q24.C, X43.3

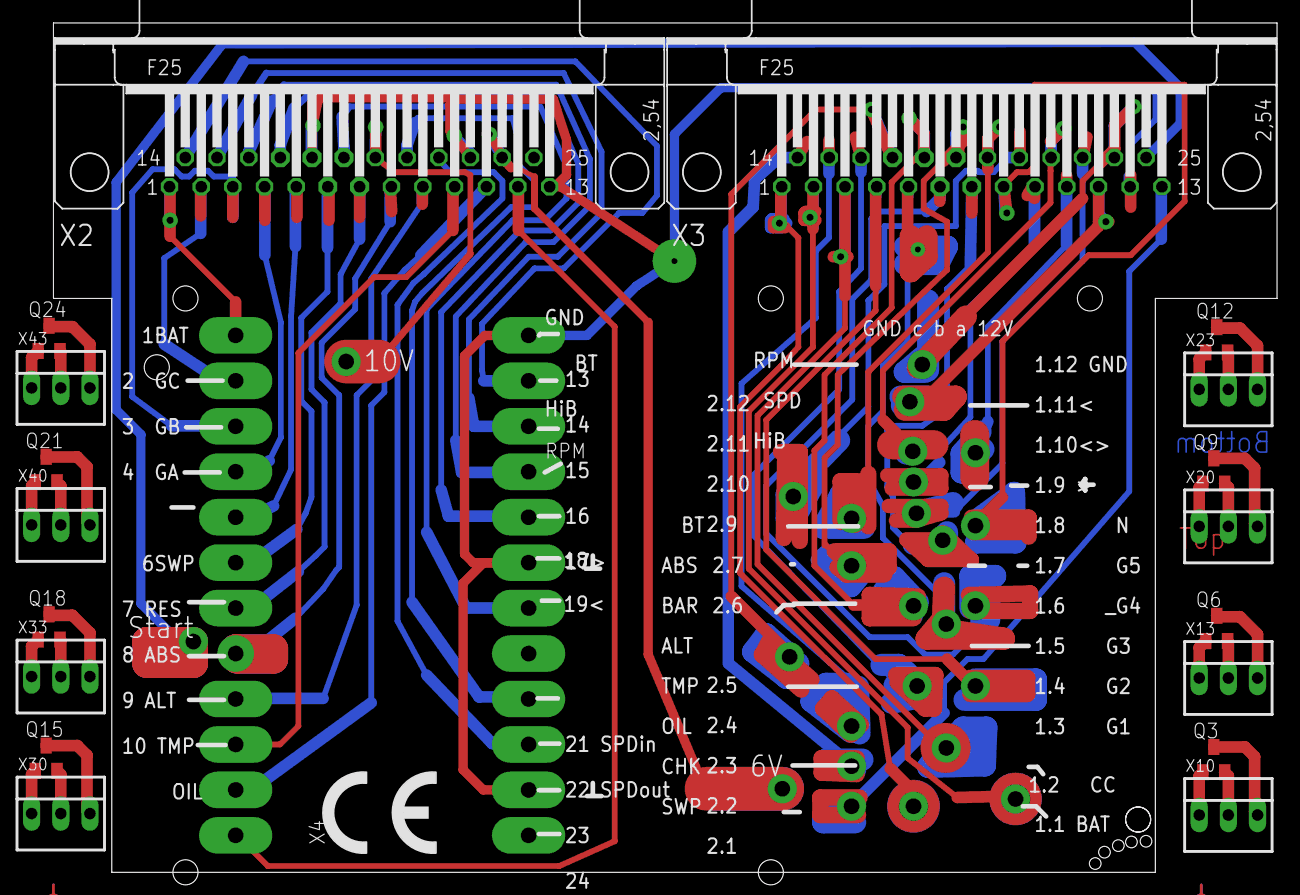
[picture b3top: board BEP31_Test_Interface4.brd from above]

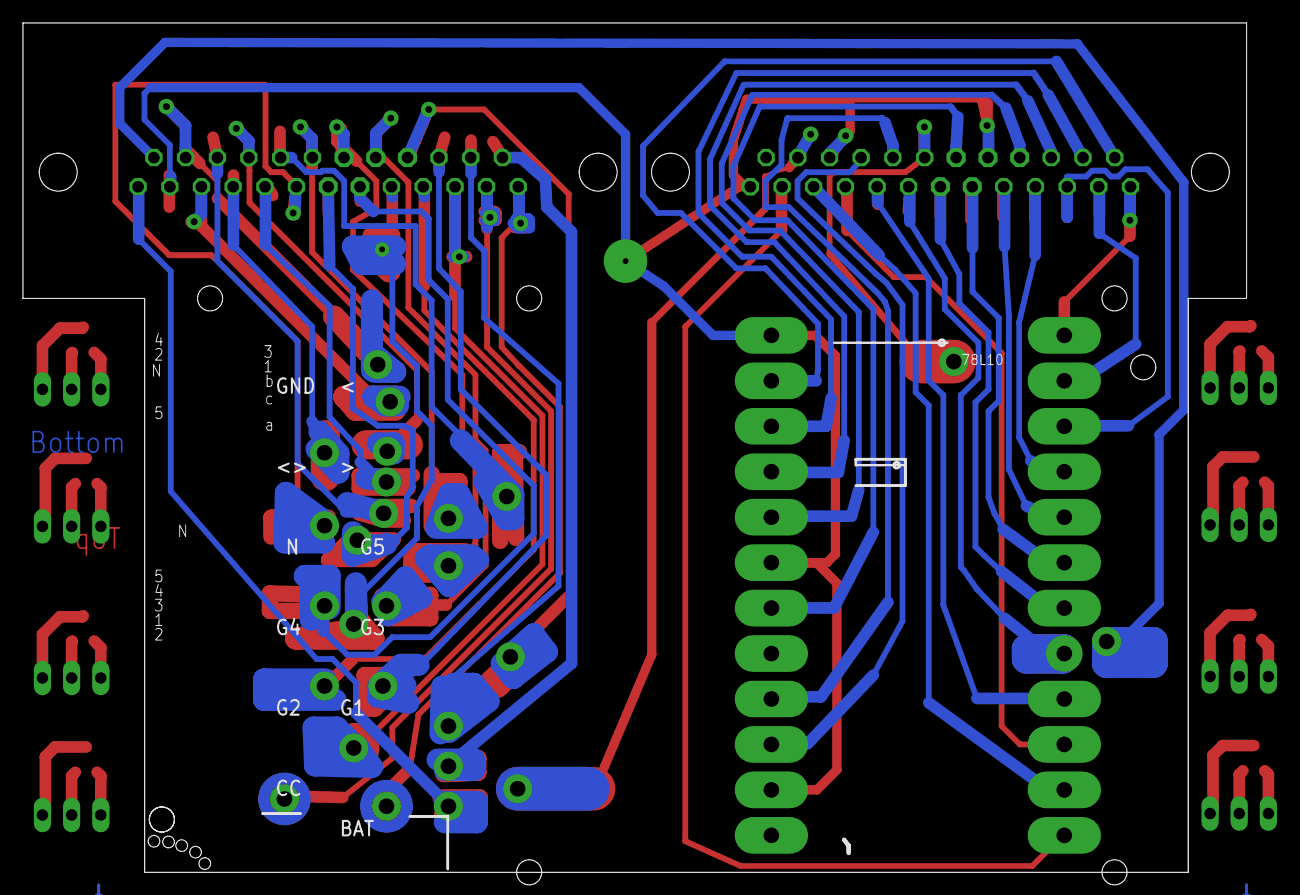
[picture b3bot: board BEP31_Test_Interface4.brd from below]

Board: 2 copper layers, 106.6 x 74.0 mm, 46 parts (23 on the bottom side), 70 nets.

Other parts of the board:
U$1: CE_10.00
